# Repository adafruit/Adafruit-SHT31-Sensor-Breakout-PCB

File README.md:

## Adafruit Sensirion SHT31-D - Temperature & Humidity Sensor PCB
<a href="http://www.adafruit.com/products/2857"><br/>
<a href="http://www.adafruit.com/products/2857"><br/>
Click here to purchase one from the Adafruit shop</a>

Sensirion Temperature/Humidity sensors are some of the finest & highest-accuracy devices you can get. And, finally we have some that have a true I2C interface for easy reading. The SHT31-D sensor has an excellent ±2% relative humidity and ±0.3°C accuracy for most uses. We now use the version with a PTFE filter, it'll stay clean while still allowing humidity measurements to work

Unlike earlier SHT sensors, this sensor has a true I2C interface, and (bonus!) even with two address options. It also is 3V or 5V compliant, so you can power and communicate with it using just about any microcontroller or microcomputer.

To get you going fast, we spun up a custom made PCB with the SHT31-D and some supporting circuitry such as pullup resistors and capacitors, in the STEMMA QT form factor, making them easy to interface with. The STEMMA QT connectors on either side are compatible with the SparkFun Qwiic I2C connectors. This allows you to make solderless connections between your development board and the SHT31-D or to chain them with a wide range of other sensors and accessories using a compatible cable. QT Cable is not included, but we have a variety in the shop.

PCB files for the Sensirion SHT31 Sensor Breakout. The format is EagleCAD schematic and board layout
- https://www.adafruit.com/product/2857

### License

Adafruit invests time and resources providing this open source design, please support Adafruit and open-source hardware by purchasing products from [Adafruit](https://www.adafruit.com)!

All text above must be included in any redistribution

Designed by Limor Fried/Ladyada for Adafruit Industries.
Creative Commons Attribution/Share-Alike, all text above must be included in any redistribution. 
See license.txt for additional information.

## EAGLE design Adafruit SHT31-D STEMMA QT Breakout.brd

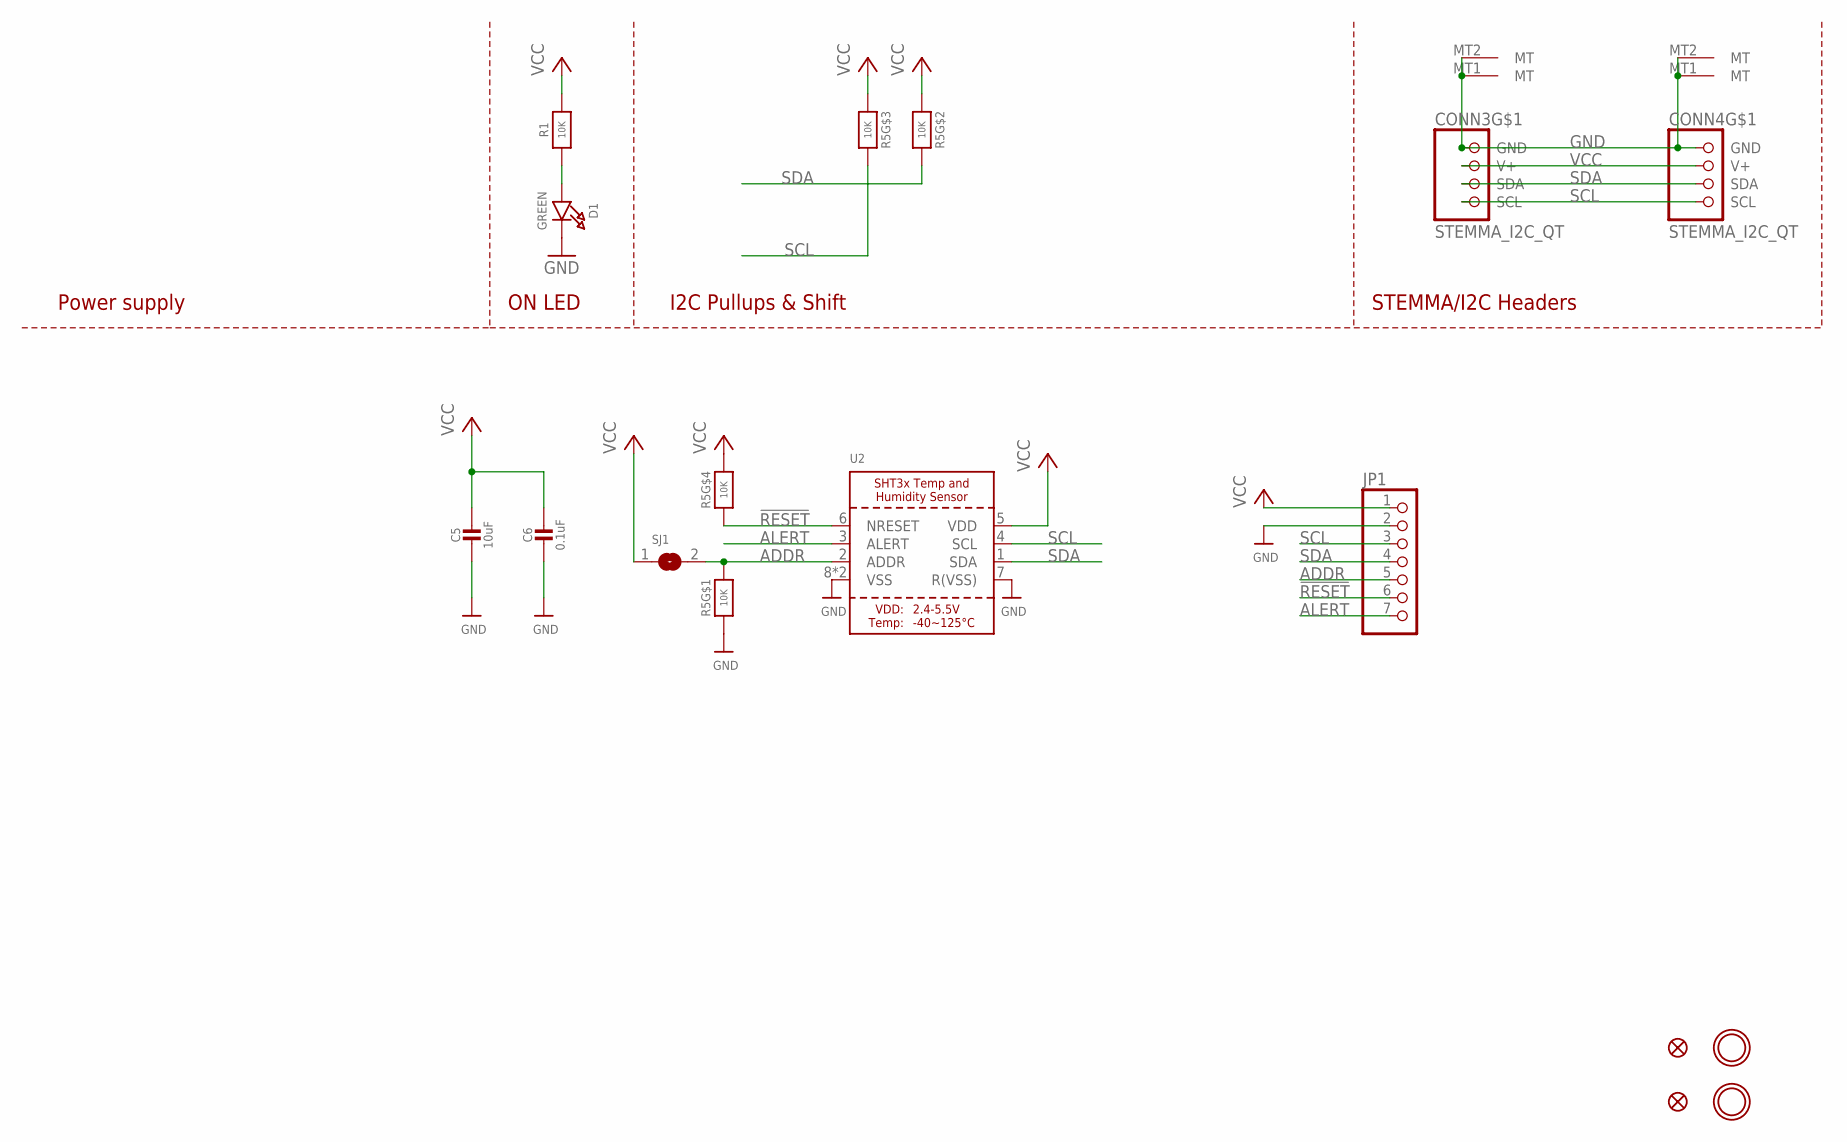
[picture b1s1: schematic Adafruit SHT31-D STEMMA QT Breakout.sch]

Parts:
C5: 10uF; 0805-NO
C6: 0.1uF; 0603-NO
CONN3, CONN4: STEMMA_I2C_QT; JST_SH4
D1: GREEN; CHIPLED_0603_NOOUTLINE
FID3, FID4: FIDUCIAL_1MM
JP1: HEADER-1X770MIL; 1X07_ROUND_70
R1: 10K; 0603-NO
R5: 10K; RESPACK_4X0603
SJ1: SOLDERJUMPER; SOLDERJUMPER_ARROW_NOPASTE
U2: SHT3X
U$19, U$20: MOUNTINGHOLE2.5; MOUNTINGHOLE_2.5_PLATED

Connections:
!RESET: JP1.6, R5.4 (1), U2.6 (NRESET)
ADDR: JP1.5, R5.8 (2), SJ1.2, U2.2 (ADDR)
ALERT: JP1.7, U2.3 (ALERT)
GND: C5.2, C6.2, CONN3.1 (GND), CONN3.MT1 (MT), CONN3.MT2 (MT), CONN4.1 (GND), CONN4.MT1 (MT), CONN4.MT2 (MT), D1.C, JP1.2, R5.1, U2.7 (R(VSS)), U2.8 (VSS), U2.THERMAL (VSS)
unnamed: D1.A, R1.1
SCL: CONN3.4 (SCL), CONN4.4 (SCL), JP1.3, R5.6 (2), U2.4 (SCL)
SDA: CONN3.3 (SDA), CONN4.3 (SDA), JP1.4, R5.7 (2), U2.1 (SDA)
VCC: C5.1, C6.1, CONN3.2 (V+), CONN4.2 (V+), JP1.1, R1.2, R5.2 (1), R5.3 (1), R5.5 (2), SJ1.1, U2.5 (VDD)

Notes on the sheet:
I2C Pullups & Shift
STEMMA/I2C Headers
ON LED
Power supply

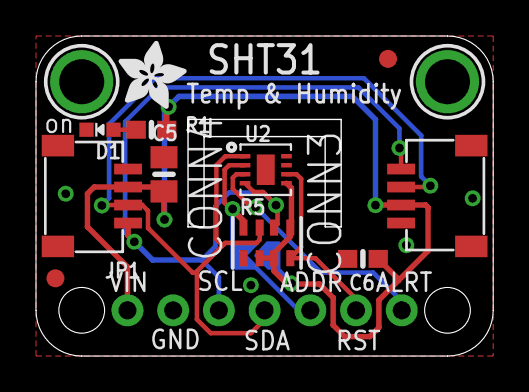
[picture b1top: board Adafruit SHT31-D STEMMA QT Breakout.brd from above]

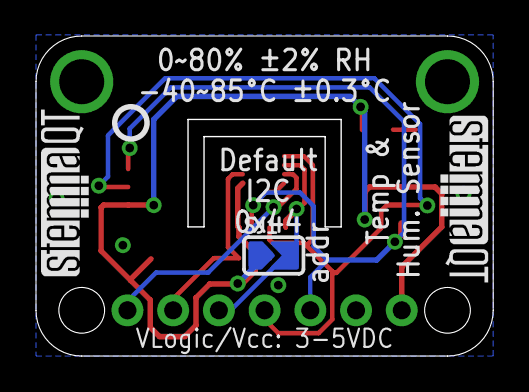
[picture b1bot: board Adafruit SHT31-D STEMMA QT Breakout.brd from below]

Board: 2 copper layers, 25.3 x 17.7 mm, 18 parts (4 on the bottom side), 8 nets.

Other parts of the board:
U$28: ADAFRUIT_3.5MM
U$29: PCBFEAT-REV-040
U$30, U$31: STEMMAQT

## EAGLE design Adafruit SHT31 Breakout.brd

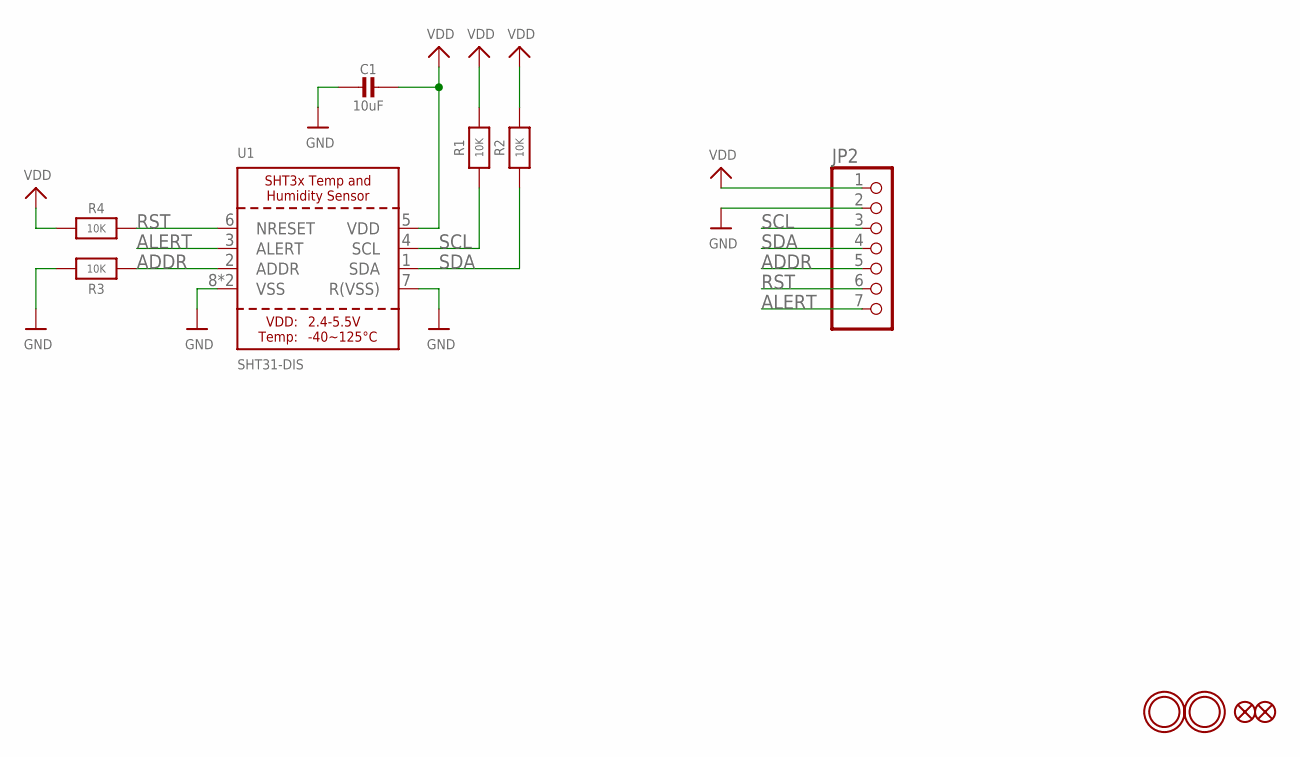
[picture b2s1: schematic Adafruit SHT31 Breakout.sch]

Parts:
C1: 10uF; 0805-NO
FID2, FID3: FIDUCIAL""; FIDUCIAL_1MM
JP2: HEADER-1X770MIL; 1X07_ROUND_70
R1, R2, R4: 10K; 0805-NO
R3: 10K; _0805MP
U1: SHT31-DIS; SHT3X
U$1, U$2: MOUNTINGHOLE2.5; MOUNTINGHOLE_2.5_PLATED

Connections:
ADDR: JP2.5, R3.1, U1.2 (ADDR)
ALERT: JP2.7, U1.3 (ALERT)
GND: C1.2, JP2.2, R3.2, U1.7 (R(VSS)), U1.8 (VSS), U1.THERMAL (VSS)
RST: JP2.6, R4.2, U1.6 (NRESET)
SCL: JP2.3, R1.1, U1.4 (SCL)
SDA: JP2.4, R2.1, U1.1 (SDA)
VDD: C1.1, JP2.1, R1.2, R2.2, R4.1, U1.5 (VDD)

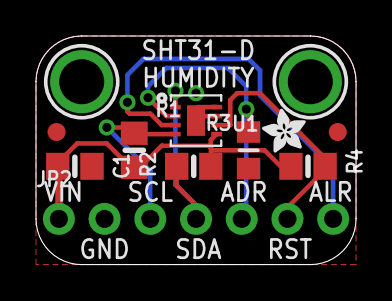
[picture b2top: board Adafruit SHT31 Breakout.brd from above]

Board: 2 copper layers, 17.8 x 12.7 mm, 13 parts (1 on the bottom side), 7 nets.

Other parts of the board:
U$11: PCBFEAT-REV-040
U$13: ADAFRUIT_2.5MM

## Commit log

2016-06-24 initied
2021-04-14 Adding QT board files.

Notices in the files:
parts and their libraries:
microbuilder: This work is placed in the public domain, and may be freely used for commercial and non-commercial work with the following conditions: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
